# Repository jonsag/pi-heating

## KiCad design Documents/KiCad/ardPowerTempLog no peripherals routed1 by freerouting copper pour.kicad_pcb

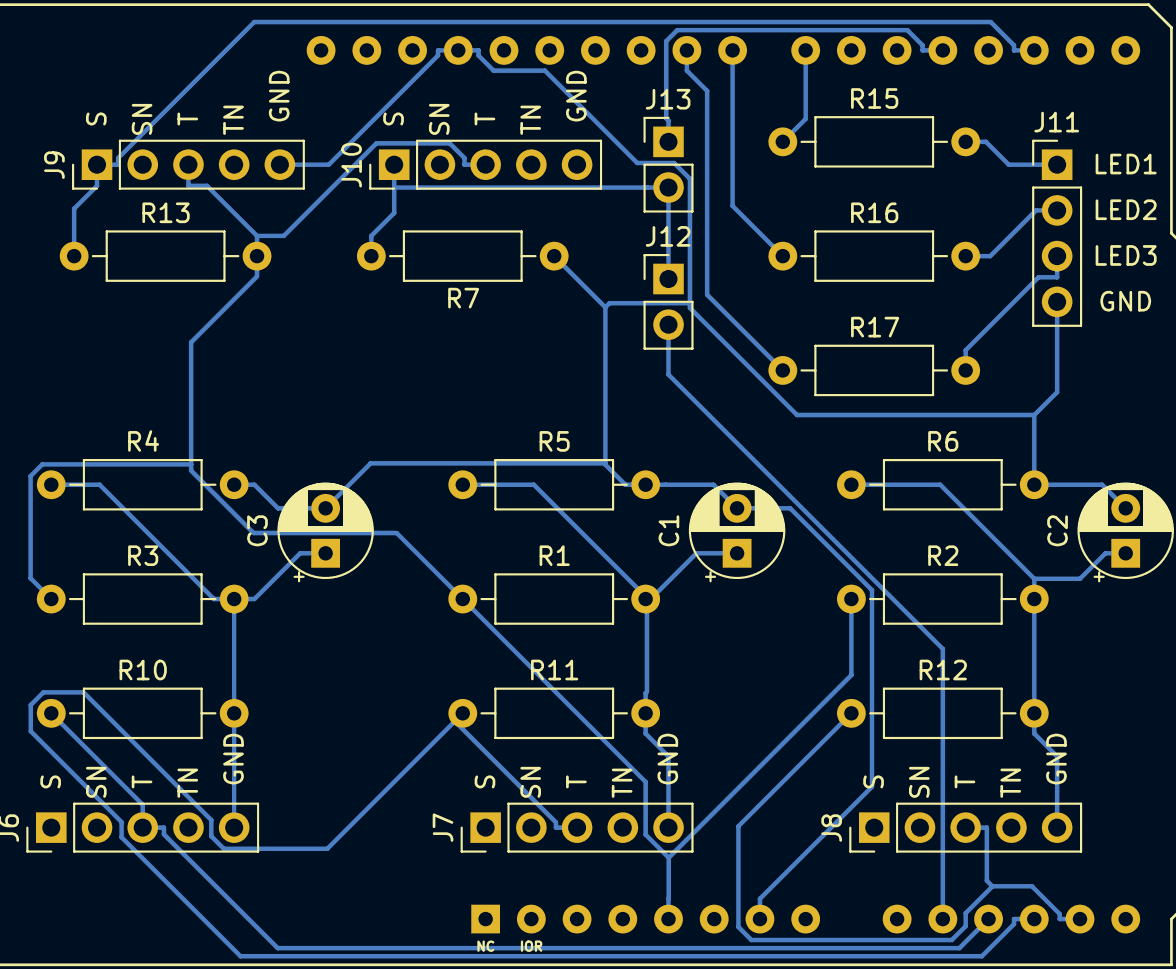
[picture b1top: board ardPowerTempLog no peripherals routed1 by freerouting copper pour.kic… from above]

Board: 2 copper layers, 26 parts (0 on the bottom side), 18 nets.

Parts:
A1: Arduino_UNO_R3; Arduino_UNO_R3_shield
C1, C2, C3: 10u; CP_Radial_D5.0mm_P2.50mm
J6, J7, J8, J9, J10: 5-pin_3-pole_3,5mm_audio_header; 5-pin_3,5mm_audio_jack_header
J11: 4-pin_3LED_header; 4-pin_3_LED_header
J12, J13: Conn_01x02_Male; PinHeader_1x02_P2.54mm_Vertical
R1, R2, R3, R4, R5: 10k; R_Axial_DIN0207_L6.3mm_D2.5mm_P10.16mm_Horizontal
R6: 100k; R_Axial_DIN0207_L6.3mm_D2.5mm_P10.16mm_Horizontal
R7: 1k; R_Axial_DIN0207_L6.3mm_D2.5mm_P10.16mm_Horizontal
R10, R11, R12: 33R; R_Axial_DIN0207_L6.3mm_D2.5mm_P10.16mm_Horizontal
R13: 4.7k; R_Axial_DIN0207_L6.3mm_D2.5mm_P10.16mm_Horizontal
R15, R16, R17: 220R; R_Axial_DIN0207_L6.3mm_D2.5mm_P10.16mm_Horizontal

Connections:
/Collector: A1.5, J9.3, J10.3, R1.1, R2.1, R3.1, R13.2
/Data: A1.17, J9.1, R13.1
/Emitter: J10.1, J12.1, J13.2, R7.2
/GND: A1.7, A1.29, C1.2, C2.2, C3.2, J9.5, J11.4, R4.2, R5.2, R6.2, R7.1
unnamed: A1.10, J12.2
unnamed: A1.11, J6.3, R10.1
unnamed: A1.12, J7.3, R11.1
unnamed: A1.13, J8.3, R12.1
unnamed: A1.19, J13.1
unnamed: A1.22, R15.1
unnamed: A1.23, R16.1
unnamed: A1.24, R17.1
unnamed: C1.1, J7.5, R1.2, R5.1, R11.2
unnamed: C2.1, J8.5, R2.2, R6.1, R12.2
unnamed: C3.1, J6.5, R3.2, R4.1, R10.2
unnamed: J11.1, R15.2
unnamed: J11.2, R16.2
unnamed: J11.3, R17.2
